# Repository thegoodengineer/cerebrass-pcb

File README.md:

# ClawBoard

An autonomous PCB design-review agent. It reads a KiCad project, runs real DFM and ERC
checks, repairs the schematic and board in place, and shows the board changing live while it
works. The agent harness is **OpenClaw**; the model is **Moonshot Kimi K3.1 Pro on Cerebras**
(`moonshotai-kimi-k3.1-pro-trial`).

```
 ┌──────────────┐   chat.completions    ┌─────────────────────────────┐
 │   OpenClaw   │ ───────────────────▶  │ Cerebras  api.cerebras.ai/v1 │
 │ agent harness│ ◀─── tool calls ───   │ moonshotai-kimi-k3.1-pro-trial│
 └──────┬───────┘                       └─────────────────────────────┘
        │ MCP (stdio)
 ┌──────▼──────────────────────────────────────────────┐      ┌───────────────────────┐
 │ pcb-tools  (Python, standard library only)          │      │ web  (Vite + React)   │
 │  inspect_kicad_project   run_dfm_and_erc_audit      │ SVG  │  live board viewer    │
 │  apply_pcb_patch         render_board_svg           │ ───▶ │  agent trace, TPS,    │
 │  S-expr parser · router · rule engine · renderer    │      │  benchmark lanes      │
 └──────┬──────────────────────────────────────────────┘      └───────────────────────┘
        │ reads / writes
   *.kicad_sch  *.kicad_pcb   (open natively in KiCad 8 / 9 / 10)
```

## Quick start

```bash
./setup.sh                 # Windows PowerShell: ./setup.ps1
# put CEREBRAS_API_KEY (and BASELINE_* for the benchmark) in .env
npm run dev                # http://localhost:3000
```

No key yet? Tick **Simulated** in the top bar. It runs the complete loop (real tools, real
board edits) against a scripted model with synthetic timing, and watermarks everything
`SIMULATED`. It is for rehearsal only and is never a benchmark result.

Requirements: Python 3.10+, Node 18+ for the dashboard. OpenClaw itself needs Node 24.16+.
KiCad is optional (it enables the independent DRC/ERC check).

## What is in the box

| Path | What |
|---|---|
| `pcb-tools/` | The tool server: `mcp_server.py` (MCP over stdio), `cli.py`, the `clawboard` package, fab and datasheet rules, tests |
| `sample_board/` | ESP32-S3 USB-C sensor + motor controller with six planted bugs (generated by `pcb-tools/make_sample_board.py`) |
| `web/` | Dashboard on `localhost:3000`, plus the run controller, metering proxy and simulated endpoint |
| `openclaw_config/` | `openclaw.json`, the agent workspace (`AGENTS.md` = the static system prompt) and the `clawboard-pcb` skill |
| `setup.sh` / `setup.ps1` | Environment check, install, self-test, OpenClaw config resolution |
| `DEMO_SCRIPT.md` | 45-second shot list for the recording |

## The four tools

| Tool | Returns |
|---|---|
| `inspect_kicad_project(project_dir)` | Components, nets with pin names, track widths, vias, drills, zones, tightest clearance, unrouted airwires. About 1.5k tokens for the sample; never raw S-expressions. |
| `run_dfm_and_erc_audit(project_dir, fab_house="jlcpcb")` | `pass`, counts, and `issues[]` with `id`, `rule`, `severity`, `title`, `detail`, `refs`, `nets`, `at`, `fix`. |
| `apply_pcb_patch(project_dir, operations)` | Per-operation result, the error count after each step, and a final audit summary. |
| `render_board_svg(project_dir)` | Writes `web/public/board_preview.svg` and `schematic_preview.svg`. Runs automatically after every audit and patch. |

**Rules checked:** USB-C CC pull-downs, decoupling per IC supply pin (value and distance, from
`rules/parts.json`), I2C pull-ups, floating pins, schematic/PCB sync, fab minimum track width,
power track width (IPC-2221), copper clearance and shorts, unrouted nets, ground-pour islands,
via geometry, copper-to-edge, placement grid, courtyard overlap.

**Patch operations:** `set_pin_net`, `add_component`, `move_footprint`, `set_track_width`,
`route_net`, `reroute_net`, `ripup_net`, `move_via`, `delete_via`, `add_via`, `add_track`,
`stitch_pour`, `rename_net`, `set_value`.

The agent states intent ("100 nF from +3V3 to GND near U1.2"). The tool solves the geometry:
it finds the nearest free grid spot whose pads clear every other net, and routes with an A*
maze router (0.25 mm grid, Manhattan and 45 degree moves, both copper layers, vias when
needed). Every new primitive is re-checked with exact geometry before it is committed.

Try them by hand:

```bash
python pcb-tools/cli.py audit sample_board --pretty
python pcb-tools/cli.py patch sample_board --ops '[{"op":"route_net","net":"UART_TX"}]' --pretty
python pcb-tools/cli.py oracle sample_board --pretty     # KiCad's own DRC/ERC
python pcb-tools/make_sample_board.py                    # regenerate the broken board
```

## The sample board and its six bugs

ESP32-S3-WROOM-1, USB-C input, AMS1117-3.3, BME280 on I2C, DRV8833 motor driver. 64 x 44 mm,
2 layers, ground pours on both sides, 25 footprints.

| # | Bug | Audit id |
|---|---|---|
| 1 | USB-C CC1 and CC2 tied together on one 5.1k resistor | `USB-CC-J1` |
| 2 | No 100 nF decoupling capacitor at the ESP32 3V3 pin | `DECAP-U1-100nF` |
| 3 | No pull-ups on I2C SDA / SCL | `I2C-PU-I2C_SDA`, `I2C-PU-I2C_SCL` |
| 4 | `+5V_VBUS` routed at 0.1 mm instead of 0.5 mm | `PWR-W-+5V_VBUS` |
| 5 | GND via 0.05 mm from a signal track | `CLR-GND-UART_RX` |
| 6 | `UART_TX` unrouted; the BME280 decoupler 19 mm away and off-grid | `UNROUTED-UART_TX`, `DECAP-FAR-C5`, `PLACE-GRID-C5` |

The project ships its own symbol and footprint library plus a `.kicad_dru`, so opening it in
KiCad and running DRC shows the same faults.

## Dashboard

- **Left:** live PCB and schematic viewer. Patched copper glows green/cyan and draws itself
  in; open DFM errors pulse red. Scroll to zoom, drag to pan, hover a net to trace it, switch
  F.Cu / B.Cu / both.
- **Right:** agent execution trace (each model call with tokens, tokens/sec and first-token
  time; each tool call; each patch operation with the errors left after it), the measured
  error-count chart, and the verification ladder.
- **Top bar:** `Run audit & fix`, and `Cerebras vs. Standard GPU`, which runs the identical
  task on both endpoints side by side.

### How the benchmark is measured

- Both lanes get the same system prompt, tools, task and a fresh copy of the same board.
- **Tokens/sec** = completion tokens / time from first streamed token to end of response,
  summed over all calls. Token counts come from the API `usage` field; if an endpoint sends
  none, they are estimated from characters and the report says so.
- **LLM time**, **tool time** and **harness setup** are shown separately. Tool time is the same
  work on both lanes, so the headline ratio is LLM time.
- **Total elapsed** runs from a lane's first model request to its sign-off (model time plus tool
  time). Harness setup and Gateway warm-up are excluded because they depend on start order, not
  on the model.
- The comparison shows correctness next to speed: operations applied, audit result and the
  KiCad oracle for each lane. A fast run that leaves errors does not count as a win.
- Every run writes a per-request report (timestamps, first-token time, usage, both TPS
  definitions, audit before/after, step log, oracle). The `report.json` link on each lane opens it.

Working copies and reports live in the OS temp directory (`clawboard-runs/`) because the tools
rewrite them many times a second; set `CLAWBOARD_RUNS_DIR` to change that.

## OpenClaw wiring

`openclaw_config/openclaw.json` (validated with `openclaw config validate`, OpenClaw 2026.11.6):

- provider `cerebras` -> `https://api.cerebras.ai/v1`, `api: "openai-completions"`,
  `apiKey: "${CEREBRAS_API_KEY}"`, model `moonshotai-kimi-k3.1-pro-trial`
- agent `clawboard` under `agents.entries`, workspace `openclaw_config/workspace`
- MCP server `clawboard-pcb` -> `python pcb-tools/mcp_server.py`
- `tools`: `toolSearch: false`, `codeMode: false`, `allow: ["clawboard-pcb__*"]`
- skill directory `openclaw_config/skills`

The `tools` block matters. By default OpenClaw hides MCP tools behind `tool_search` /
`tool_describe`, and with that switched off it sends all of its roughly 50 built-in tools
(about 36k tokens per request). Allowing only `clawboard-pcb__*` puts exactly the four PCB tools
in the model's tool list, keeps each request near 10k tokens, and means the agent cannot run
shell commands or edit files on your machine. Widen `tools.allow` if you want the skill's
command-line fallback.

`setup` writes `openclaw.resolved.json` with absolute paths. One-shot use from a terminal:

```bash
export OPENCLAW_CONFIG_PATH="$PWD/openclaw_config/openclaw.resolved.json"
export CEREBRAS_API_KEY=...
openclaw config validate
openclaw mcp doctor clawboard-pcb --probe
openclaw agent exec --config "$OPENCLAW_CONFIG_PATH" --cwd "$PWD/openclaw_config/workspace" --json \
  "Audit and repair the KiCad project in project_dir: $PWD/sample_board"
```

### How the dashboard drives OpenClaw

`openclaw agent exec` re-loads OpenClaw's plugin registry on every call (60-100 s on the
development laptop), which is no use for a live demo. So the dashboard keeps one **OpenClaw
Gateway** warm and starts each agent turn with a single HTTP request to the Gateway's
OpenAI-compatible endpoint:

1. On start-up the dashboard launches `openclaw gateway` on `127.0.0.1:18931` with a generated
   runtime config (its own state directory under the temp folder, a random token, one agent per
   benchmark lane, `gateway.http.endpoints.chatCompletions.enabled: true`). The status strip
   shows `OpenClaw gateway: warming up` and then `ready`; the first start takes one to three minutes.
2. Each lane's run is `POST /v1/chat/completions` with `model: "openclaw/clawboard-<lane>"`.
   OpenClaw runs the whole agent turn (prompt assembly, model calls, MCP tool calls) and returns
   the sign-off.
3. In the runtime config each lane's provider points at a local pass-through
   (`/llm/<lane>/v1`) that forwards every request to the real endpoint unchanged and meters the
   stream. That is where the live tokens/sec, first-token time and token counts come from.
4. The Gateway prepares sessions one at a time, so in a comparison the second lane's turn is
   released when the first lane has sent its first model request. Each lane's **Total elapsed**
   runs from its own first model request to sign-off; **Harness setup** is shown separately.

`Engine: auto` uses OpenClaw when the CLI and Node 24.16+ are present, and otherwise a built-in
OpenAI-compatible loop with the same prompt and the same MCP server. The Gateway uses about
1.4 GB of memory while it runs; set `CLAWBOARD_NO_PREWARM=1` to start it only on first use.

### Prompt caching and the 100K TPM limit

`openclaw_config/workspace/AGENTS.md` holds everything static: workflow, operation reference,
KiCad file facts, JLCPCB 2-layer and 4-layer limits, IPC-2221 table, and datasheet rules for
ESP32-S3, STM32, USB-C, BME280, DRV8833 and AMS1117. It has no timestamps or per-run content,
so every request in a loop shares the same prefix. OpenClaw injects it into its system prompt
and puts the date and other per-run context in a later user message, so the prefix stays
cacheable. The tool schemas are static too.

Measured with the simulated endpoint (token counts are its character-based estimate, so treat
them as approximate): one full run through OpenClaw is 4 model calls, about 39k prompt tokens
in total with about 59 % of them a repeat of the previous call's prefix, and about 600
completion tokens. The built-in loop sends about 22k. On Cerebras, cached tokens count toward
the total-TPM bucket but not the uncached one, so two runs per minute fit under 100K. A
comparison run uses the Cerebras budget once; the baseline lane has its own.

## Verification

Three rungs, reported separately and never substituted for one another:

1. **Patch post-conditions.** Every track, via and pad the patch tool adds is checked against
   all other copper with exact geometry before it is written. Files are replaced only after a
   structural integrity check, and the original is kept in `.clawboard/original/`.
2. **ClawBoard audit.** The full rule set, re-run after every operation (the measured step log).
3. **KiCad oracle.** `kicad-cli pcb drc` and `sch erc` on a copy of the project. A different
   implementation, so it cannot share our bugs. It takes 15-40 s, so it runs once after the
   agent signs off and is not part of the timed loop.

Measured on this machine (KiCad 10.0.4, `python pcb-tools/cli.py oracle`):

| Board | ClawBoard audit | KiCad DRC | KiCad unconnected | KiCad ERC |
|---|---|---|---|---|
| `sample_board` as shipped | 8 errors, 1 warning | 29 errors (1 clearance, 28 track width) | 1 (`UART_TX`) | 0 errors |
| after the nine-operation fix | 0 errors, 0 warnings | 0 errors | 0 | 0 errors |

KiCad also reports about 80 silkscreen warnings (reference text over pads) on both; they are
cosmetic and unrelated to the planted bugs.

```bash
npm test        # 9 tests: parser round-trip, netlist sync, the six bugs, the fix, MCP protocol
```

## Design principles

| Principle | Where it is here |
|---|---|
| Verify in separate stages and never report one stage's result as another's | The three rungs above; the agent prompt forbids claiming the KiCad result |
| Every number is backed by a record | Per-request `report.json` behind every lane; simulated runs are labelled in the UI and in the report |
| Report correctness next to speed | The benchmark shows audit and oracle status per lane, not only tokens/sec |
| Measure every step | Error count before and after every patch operation, drawn as the step chart |
| Keep the inner loop fast; run expensive checks once at the end | Audit inside the patch call (no extra model round trip); KiCad DRC once after sign-off |
| Reject bad data instead of using it | Integrity-checked writes, rejected operations with reasons, pristine backup |
| People define what correct means; the agent explores | The static contract in `AGENTS.md`; audit `fix` hints are suggestions, not orders |
| Cut per-call overhead | One persistent MCP tool process per run instead of a new interpreter per call |

## What has and has not been verified

Verified on the development machine (Windows 11, Python 3.12, Node 24.22.3, OpenClaw 2026.11.6, KiCad 10.0.4):

- the test suite, the sample generator, and the full fix cycle
- KiCad's DRC/ERC opening both files and agreeing with the audit, before and after
- `openclaw config validate`, `openclaw mcp doctor clawboard-pcb --probe`, and a complete
  `openclaw agent exec` run
- **live**: Kimi K3.1 Pro (`moonshotai-kimi-k3.1-pro-trial`) on Cerebras driving the agent through
  the OpenClaw Gateway. One patch of 9 operations took the board from 8 errors to 0, KiCad
  reported 0 DRC errors, 0 unconnected items and 0 ERC errors, and the run measured 591
  tokens/sec with 68 % of prompt tokens served from the prompt cache (4 model calls, 14.2 s
  from first model request to sign-off, during a period when the trial endpoint was returning
  "high traffic" 429s that the dashboard retried)
- the same live model through the built-in loop
- both benchmark lanes through OpenClaw and through the built-in loop, using the Simulated endpoint

Still not verified:

- a baseline endpoint for the comparison lane (none was configured), so no live
  Cerebras-versus-GPU ratio has been measured
- the model's context window in `openclaw.json` (131072) is a placeholder: set the real value.

## Limits

- Footprints are simplified land patterns generated by `clawboard/library.py`. Check them
  against vendor drawings before fabricating anything.
- The schematic reader handles a single flat sheet (wires, junctions, labels, power symbols);
  hierarchical sheets and buses are not supported.
- The board outline is treated as its bounding rectangle. Arcs, zones with cut-outs and
  blind/buried vias are not modelled.
- The pour model is a conservative 0.25 mm-grid approximation of KiCad's zone fill. Zones are
  written unfilled: press `B` in KiCad to fill them.
- JLCPCB numbers in `rules/jlcpcb.json` were read from their capabilities page on 2026-11-22.
  Confirm them before ordering.
- Tool time (about 4 s for the nine-operation patch) is pure-Python geometry. It is the same
  on every lane, but it does bound the end-to-end speed-up.

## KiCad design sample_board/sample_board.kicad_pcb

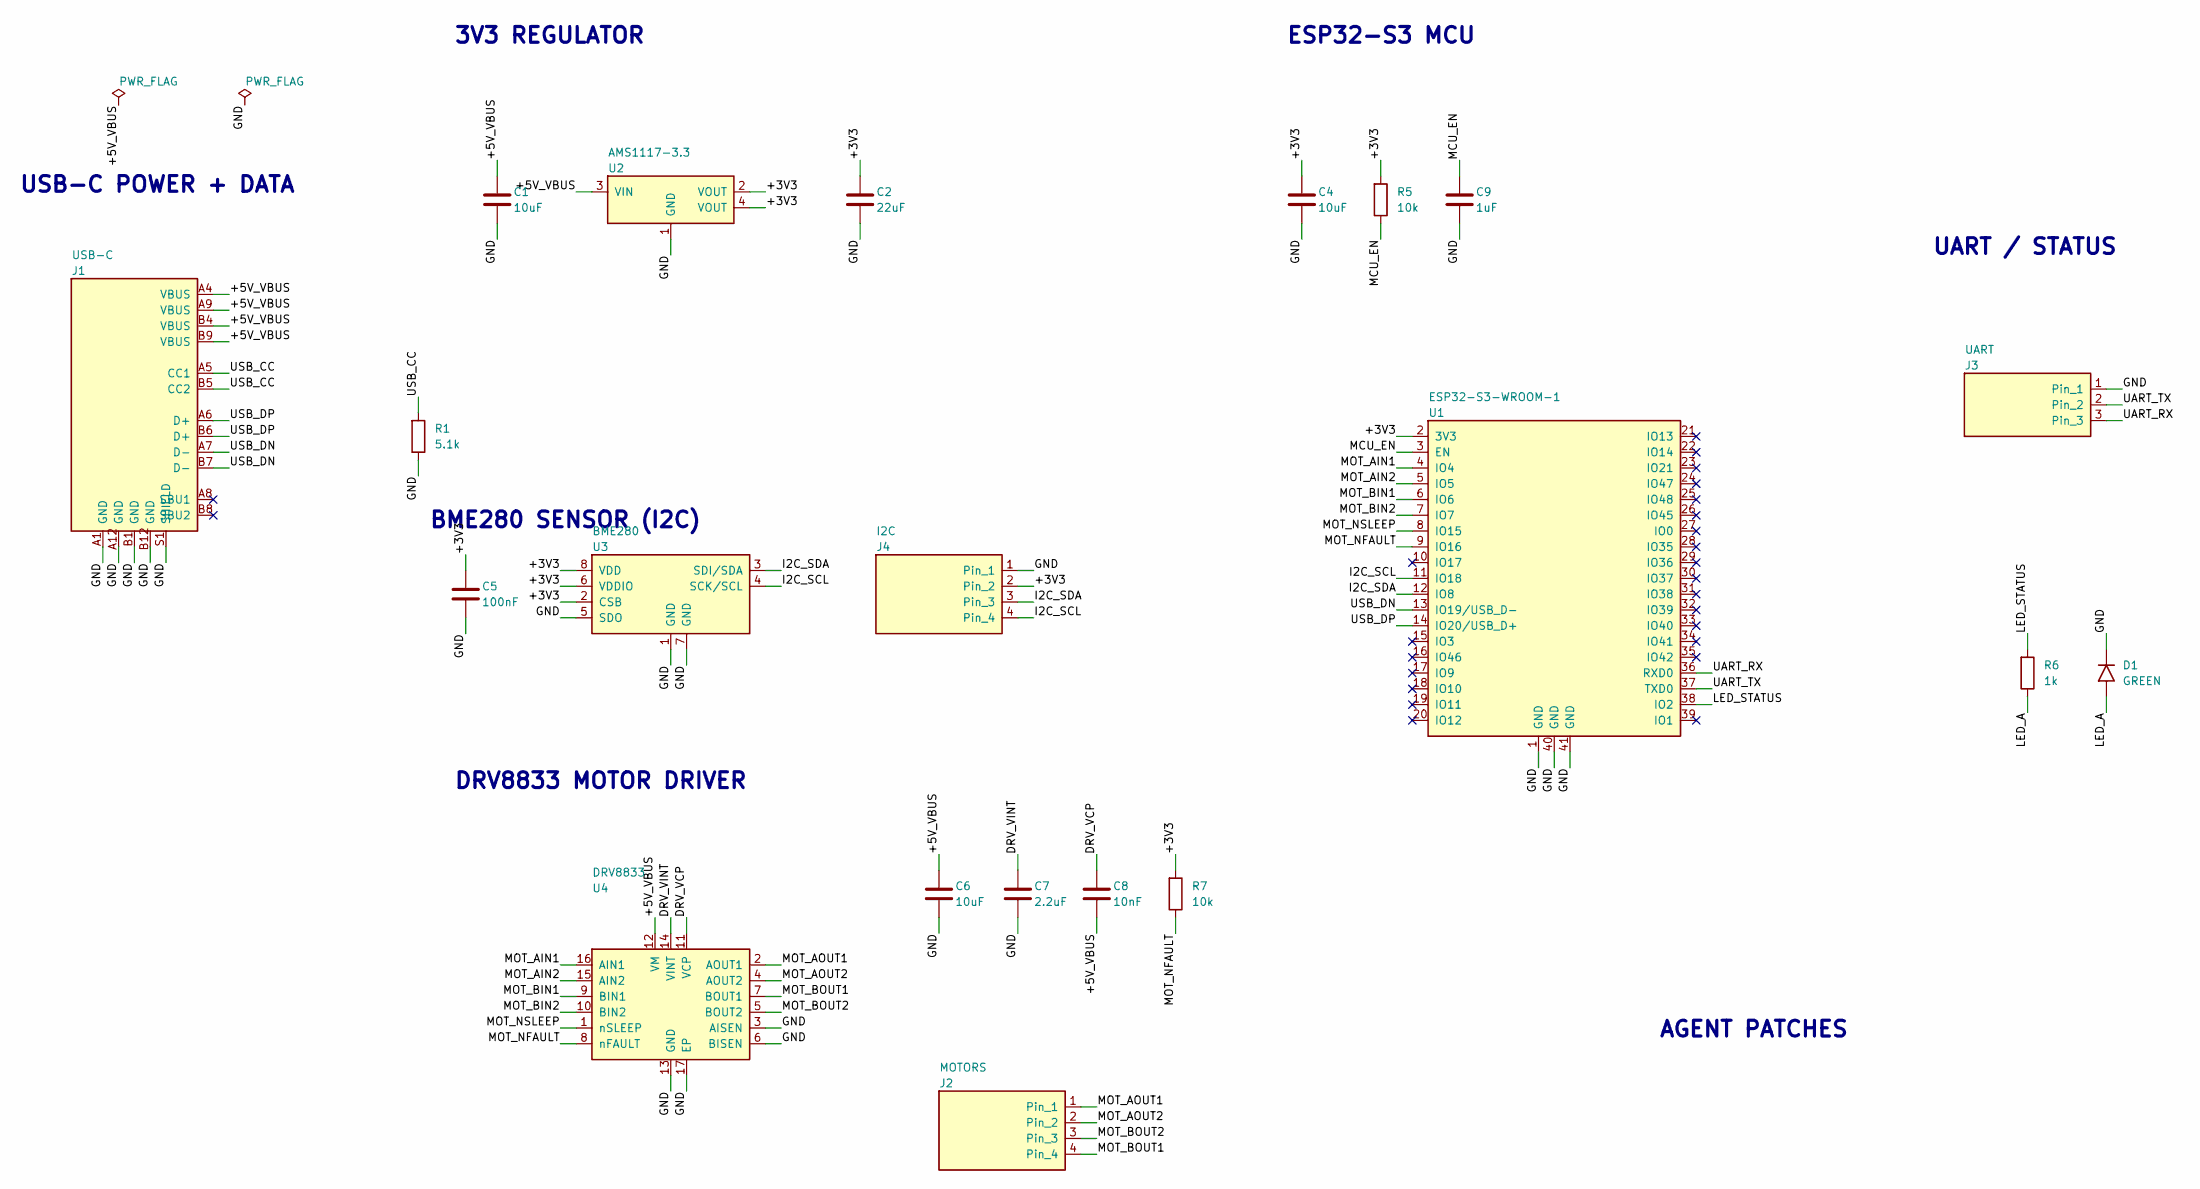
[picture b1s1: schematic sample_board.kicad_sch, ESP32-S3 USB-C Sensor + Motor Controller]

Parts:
C1, C4, C6: 10uF; C_0805
C2: 22uF; C_0805
C5: 100nF; C_0603
C7: 2.2uF; C_0603
C8: 10nF; C_0603
C9: 1uF; C_0603
D1: GREEN; LED_0603
J1: USB-C; USB_C_Receptacle_16P
J2: MOTORS; PinHeader_1x04_P2.54mm
J3: UART; PinHeader_1x03_P2.54mm
J4: I2C; PinHeader_1x04_P2.54mm
R1: 5.1k; R_0603
R5, R7: 10k; R_0603
R6: 1k; R_0603
U1: ESP32-S3-WROOM-1
U2: AMS1117-3.3; SOT-223-3_TabPin2
U3: BME280; Bosch_LGA-8_2.5x2.5mm_P0.65mm
U4: DRV8833; HTSSOP-16-1EP_4.4x5mm_P0.65mm

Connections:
+3V3: C2.1, C4.1, C5.1, J4.2, R5.1, R7.1, U1.2 (3V3), U2.2 (VOUT), U2.4 (VOUT), U3.2 (CSB), U3.6 (VDDIO), U3.8 (VDD)
+5V_VBUS: C1.1, C6.1, C8.2, J1.A4 (VBUS), J1.A9 (VBUS), J1.B4 (VBUS), J1.B9 (VBUS), U2.3 (VIN), U4.12 (VM)
DRV_VCP: C8.1, U4.11 (VCP)
DRV_VINT: C7.1, U4.14 (VINT)
GND: C1.2, C2.2, C4.2, C5.2, C6.2, C7.2, C9.2, D1.1 (K), J1.A1 (GND), J1.A12 (GND), J1.B1 (GND), J1.B12 (GND), J1.S1 (SHIELD), J3.1, J4.1, R1.2, U1.1 (GND), U1.40 (GND), U1.41 (GND), U2.1 (GND), U3.1 (GND), U3.5 (SDO), U3.7 (GND), U4.3 (AISEN), U4.6 (BISEN), U4.13 (GND), U4.17 (EP)
I2C_SCL: J4.4, U1.11 (IO18), U3.4 (SCK/SCL)
I2C_SDA: J4.3, U1.12 (IO8), U3.3 (SDI/SDA)
LED_A: D1.2 (A), R6.2
LED_STATUS: R6.1, U1.38 (IO2)
MCU_EN: C9.1, R5.2, U1.3 (EN)
MOT_AIN1: U1.4 (IO4), U4.16 (AIN1)
MOT_AIN2: U1.5 (IO5), U4.15 (AIN2)
MOT_AOUT1: J2.1, U4.2 (AOUT1)
MOT_AOUT2: J2.2, U4.4 (AOUT2)
MOT_BIN1: U1.6 (IO6), U4.9 (BIN1)
MOT_BIN2: U1.7 (IO7), U4.10 (BIN2)
MOT_BOUT1: J2.4, U4.7 (BOUT1)
MOT_BOUT2: J2.3, U4.5 (BOUT2)
MOT_NFAULT: R7.2, U1.9 (IO16), U4.8 (nFAULT)
MOT_NSLEEP: U1.8 (IO15), U4.1 (nSLEEP)
UART_RX: J3.3, U1.36 (RXD0)
UART_TX: J3.2, U1.37 (TXD0)
USB_CC: J1.A5 (CC1), J1.B5 (CC2), R1.1
USB_DN: J1.A7 (D-), J1.B7 (D-), U1.13 (IO19/USB_D-)
USB_DP: J1.A6 (D+), J1.B6 (D+), U1.14 (IO20/USB_D+)

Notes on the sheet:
USB-C POWER + DATA
3V3 REGULATOR
BME280 SENSOR (I2C)
DRV8833 MOTOR DRIVER
ESP32-S3 MCU
UART / STATUS
AGENT PATCHES

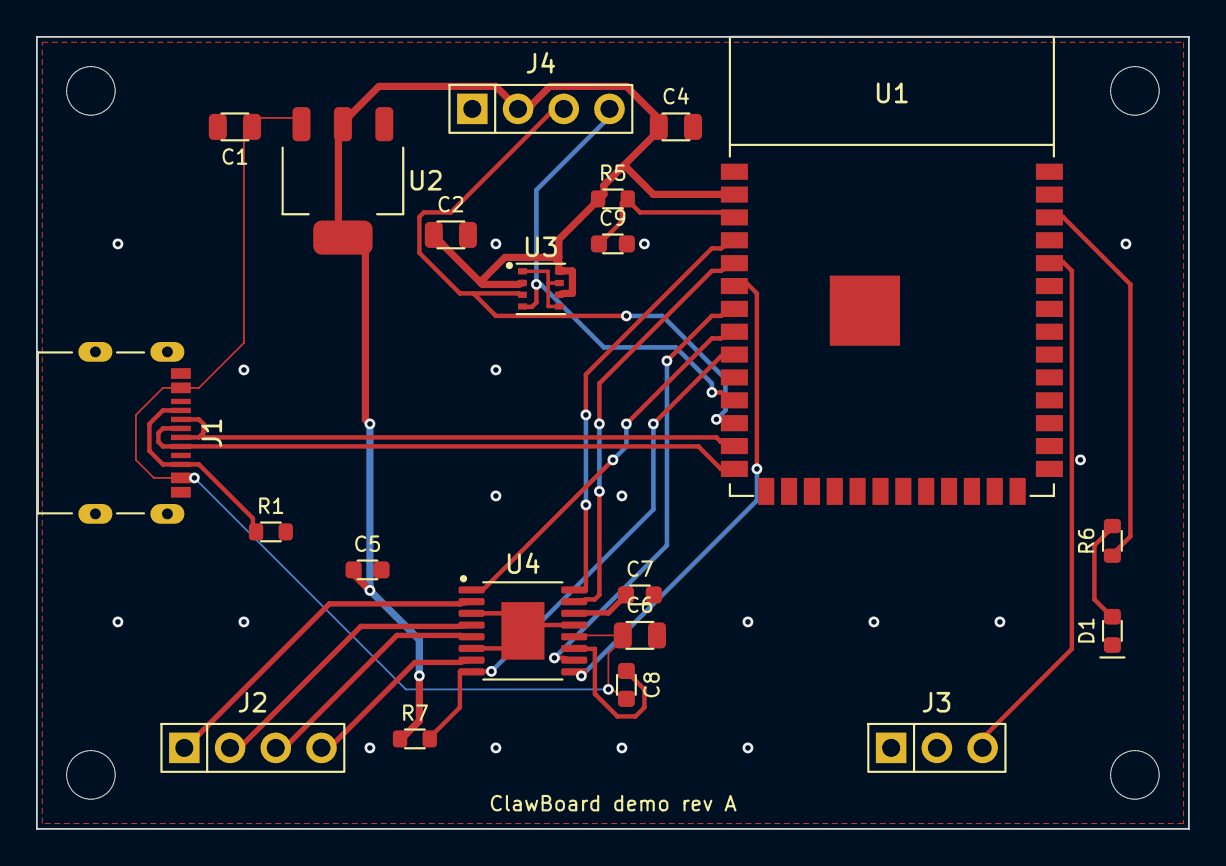
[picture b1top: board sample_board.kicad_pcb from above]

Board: 2 copper layers, 64.0 x 44.0 mm, 25 parts (0 on the bottom side), 25 nets.

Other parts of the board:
H1, H2, H3, H4: M2.5; MountingHole_2.7mm_M2.5

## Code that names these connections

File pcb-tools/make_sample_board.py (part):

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    # BUG 6b: decoupler for U3 sits ~15 mm away and off the placement grid
    ("C5", "C", "100nF", "C_0603", (18.37, 29.61, 0), (93.98, 114.3), {"1": "+3V3", "2": "GND"}),
    # BUG 3: no pull-ups (R3 / R4) on I2C_SDA / I2C_SCL
    ("J4", "Conn_01x04", "I2C", "PinHeader_1x04_P2.54mm", (28.0, 4.0, 0), (170.18, 114.3), {"1": "GND", "2": "+3V3", "3": "I2C_SDA", "4": "I2C_SCL"}),
    ("U4", "DRV8833", "DRV8833", "HTSSOP-16-1EP_4.4x5mm_P0.65mm", (27.0, 33.0, 0), (127.0, 180.34), {
        "1": "MOT_NSLEEP", "2": "MOT_AOUT1", "3": "GND", "4": "MOT_AOUT2", "5": "MOT_BOUT2", "6": "GND", "7": "MOT_BOUT1",
        "8": "MOT_NFAULT", "9": "MOT_BIN1", "10": "MOT_BIN2", "11": "DRV_VCP", "12": "+5V_VBUS", "13": "GND", "14": "DRV_VINT",
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    ("R7", "R", "10k", "R_0603", (21.0, 39.0, 0), (208.28, 162.56), {"1": "+3V3", "2": "MOT_NFAULT"}),
    ("J2", "Conn_01x04", "MOTORS", "PinHeader_1x04_P2.54mm", (12.0, 39.5, 0), (180.34, 200.66), {
        "1": "MOT_AOUT1", "2": "MOT_AOUT2", "3": "MOT_BOUT2", "4": "MOT_BOUT1"}),
    ("J3", "Conn_01x03", "UART", "PinHeader_1x03_P2.54mm", (50.0, 39.5, 0), (345.44, 83.82), {"1": "GND", "2": "UART_TX", "3": "UART_RX"}),
    ("R6", "R", "1k", "R_0603", (59.75, 28.0, 90), (345.44, 127.0), {"1": "LED_STATUS", "2": "LED_A"}),
    ("D1", "LED", "GREEN", "LED_0603", (59.75, 33.0, 90), (358.14, 127.0), {"1": "GND", "2": "LED_A"}),
]
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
